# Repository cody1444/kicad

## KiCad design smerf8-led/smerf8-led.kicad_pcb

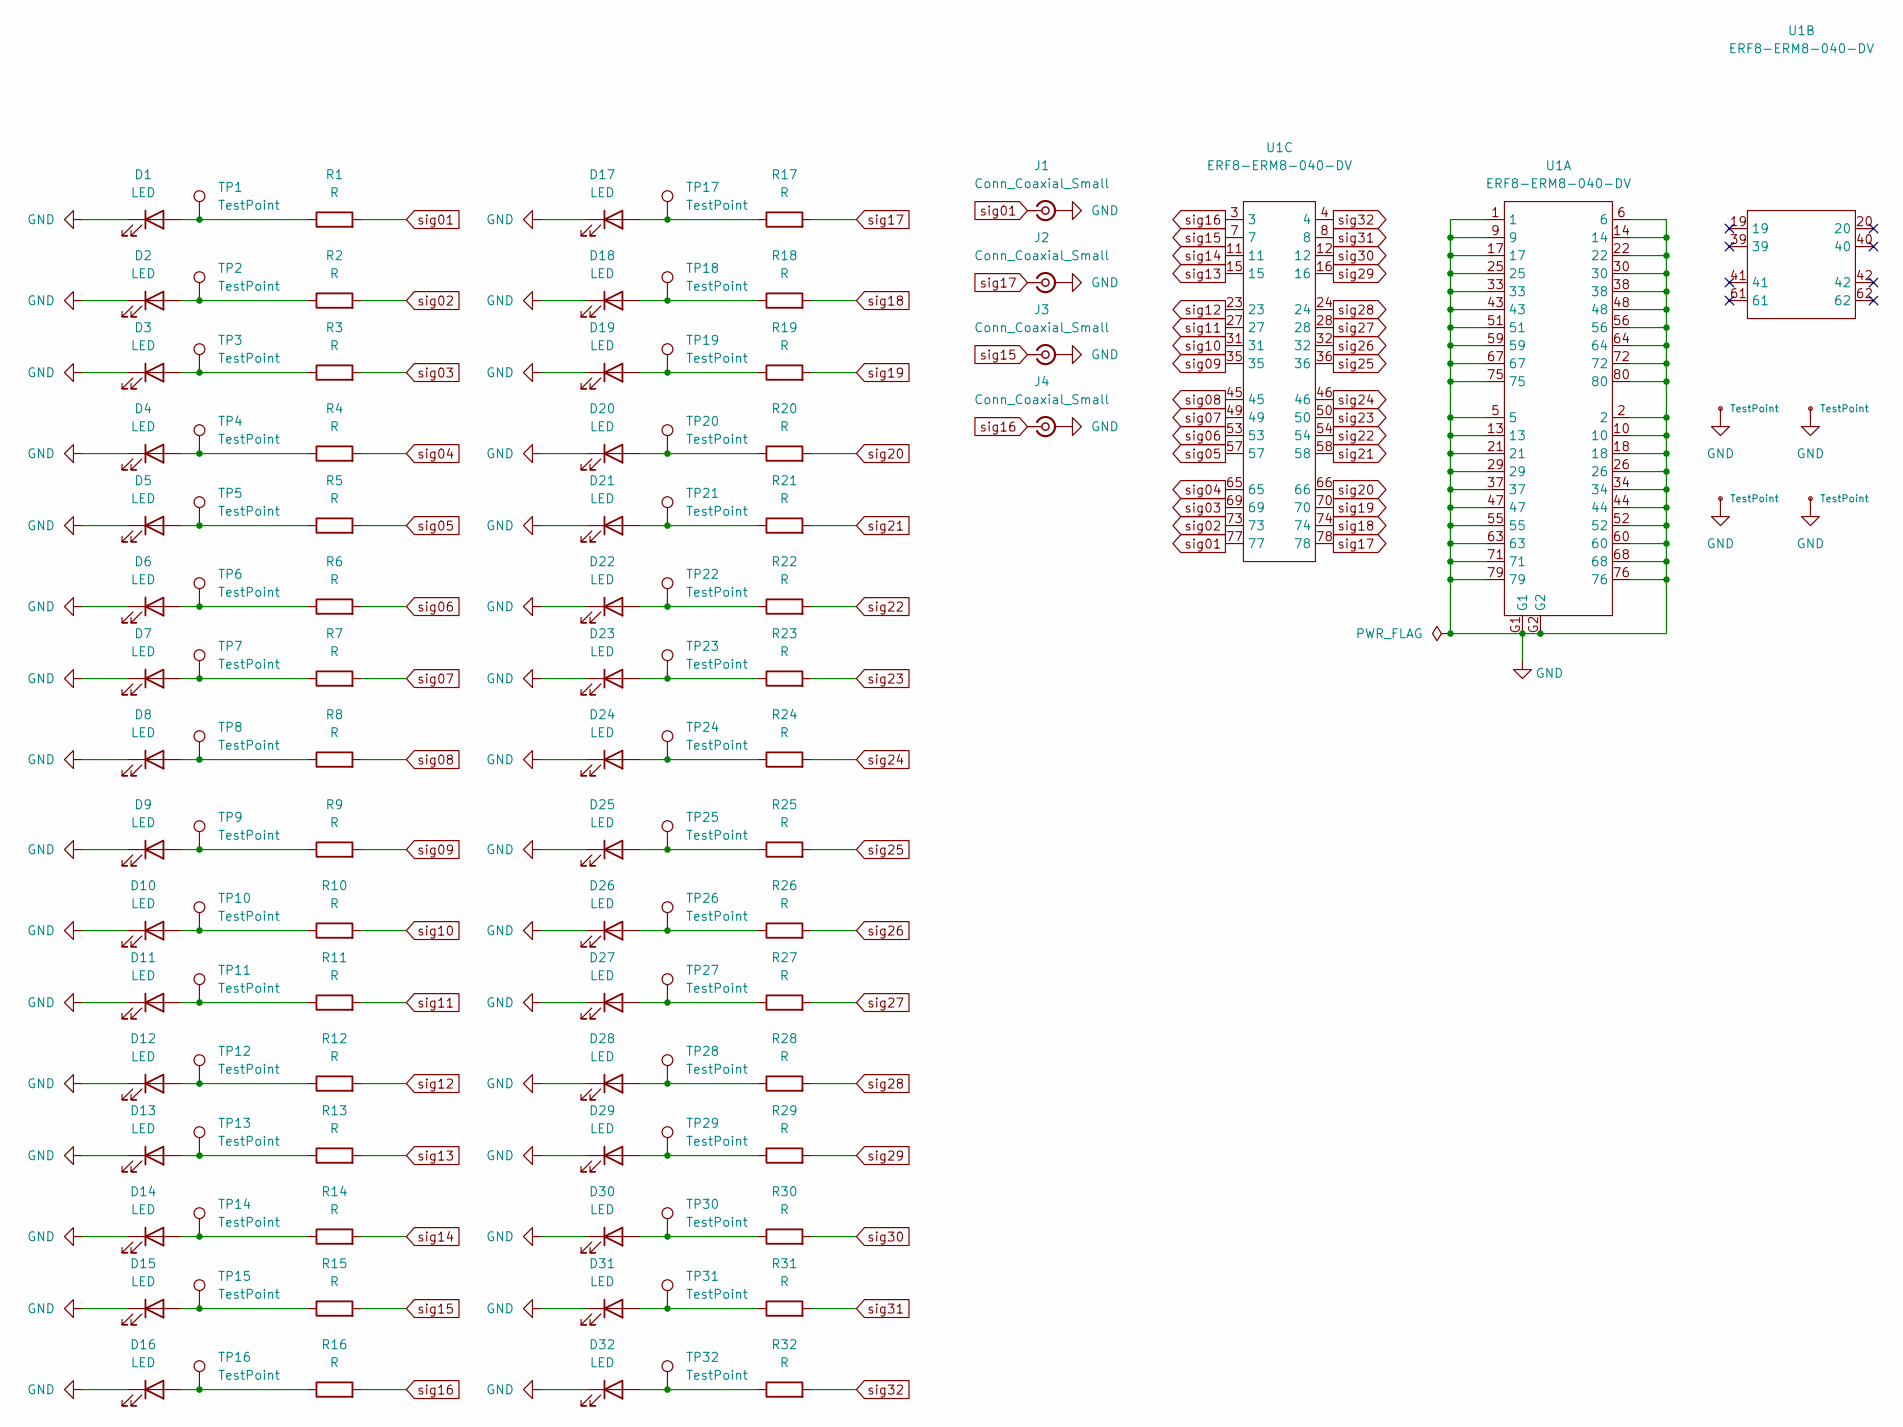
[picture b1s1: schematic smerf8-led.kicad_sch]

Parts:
D1, D2, D3, D4, D5, D6, D7, D8, D9, D10, D11, D12, D13, D14, D15, D16, D17, D18, D19, D20, D21, D22, D23, D24, D25, D26, D27, D28, D29, D30, D31, D32: LED; LED_0402_1005Metric
GND1, GND2, GND3, GND4: TestPoint; TestPoint_Plated_Hole_D2.0mm
J1, J2, J3, J4: Conn_Coaxial_Small; MMCX_Molex_73415-1471_Vertical
R1, R2, R3, R4, R5, R6, R7, R8, R9, R10, R11, R12, R13, R14, R15, R16, R17, R18, R19, R20, R21, R22, R23, R24, R25, R26, R27, R28, R29, R30, R31, R32: R; R_0603_1608Metric
TP1, TP2, TP3, TP4, TP5, TP6, TP7, TP8, TP9, TP10, TP11, TP12, TP13, TP14, TP15, TP16, TP17, TP18, TP19, TP20, TP21, TP22, TP23, TP24, TP25, TP26, TP27, TP28, TP29, TP30, TP31, TP32: TestPoint; TestPoint_Plated_Hole_D1.1mm
U1: ERF8-ERM8-040-DV; ERF8-040-EM2

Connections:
GND: D1.1 (K), D2.1 (K), D3.1 (K), D4.1 (K), D5.1 (K), D6.1 (K), D7.1 (K), D8.1 (K), D9.1 (K), D10.1 (K), D11.1 (K), D12.1 (K), D13.1 (K), D14.1 (K), D15.1 (K), D16.1 (K), D17.1 (K), D18.1 (K), D19.1 (K), D20.1 (K), D21.1 (K), D22.1 (K), D23.1 (K), D24.1 (K), D25.1 (K), D26.1 (K), D27.1 (K), D28.1 (K), D29.1 (K), D30.1 (K), D31.1 (K), D32.1 (K), GND1.1, GND2.1, GND3.1, GND4.1, J1.2 (Ext), J2.2 (Ext), J3.2 (Ext), J4.2 (Ext), U1.1, U1.2, U1.5, U1.6, U1.9, U1.10, U1.13, U1.14, U1.17, U1.18, U1.21, U1.22, U1.25, U1.26, U1.29, U1.30, U1.33, U1.34, U1.37, U1.38, U1.43, U1.44, U1.47, U1.48, U1.51, U1.52, U1.55, U1.56, U1.59, U1.60, U1.63, U1.64, U1.67, U1.68, U1.71, U1.72, U1.75, U1.76, U1.79, U1.80, U1.G1, U1.G2
unnamed: D1.2 (A), R1.1, TP1.1
unnamed: D2.2 (A), R2.1, TP2.1
unnamed: D3.2 (A), R3.1, TP3.1
unnamed: D4.2 (A), R4.1, TP4.1
unnamed: D5.2 (A), R5.1, TP5.1
unnamed: D6.2 (A), R6.1, TP6.1
unnamed: D7.2 (A), R7.1, TP7.1
unnamed: D8.2 (A), R8.1, TP8.1
unnamed: D9.2 (A), R9.1, TP9.1
unnamed: D10.2 (A), R10.1, TP10.1
unnamed: D11.2 (A), R11.1, TP11.1
unnamed: D12.2 (A), R12.1, TP12.1
unnamed: D13.2 (A), R13.1, TP13.1
unnamed: D14.2 (A), R14.1, TP14.1
unnamed: D15.2 (A), R15.1, TP15.1
unnamed: D16.2 (A), R16.1, TP16.1
unnamed: D17.2 (A), R17.1, TP17.1
unnamed: D18.2 (A), R18.1, TP18.1
unnamed: D19.2 (A), R19.1, TP19.1
unnamed: D20.2 (A), R20.1, TP20.1
unnamed: D21.2 (A), R21.1, TP21.1
unnamed: D22.2 (A), R22.1, TP22.1
unnamed: D23.2 (A), R23.1, TP23.1
unnamed: D24.2 (A), R24.1, TP24.1
unnamed: D25.2 (A), R25.1, TP25.1
unnamed: D26.2 (A), R26.1, TP26.1
unnamed: D27.2 (A), R27.1, TP27.1
unnamed: D28.2 (A), R28.1, TP28.1
unnamed: D29.2 (A), R29.1, TP29.1
unnamed: D30.2 (A), R30.1, TP30.1
unnamed: D31.2 (A), R31.1, TP31.1
unnamed: D32.2 (A), R32.1, TP32.1
sig01: J1.1 (In), R1.2, U1.77
sig02: R2.2, U1.73
sig03: R3.2, U1.69
sig04: R4.2, U1.65
sig05: R5.2, U1.57
sig06: R6.2, U1.53
sig07: R7.2, U1.49
sig08: R8.2, U1.45
sig09: R9.2, U1.35
sig10: R10.2, U1.31
sig11: R11.2, U1.27
sig12: R12.2, U1.23
sig13: R13.2, U1.15
sig14: R14.2, U1.11
sig15: J3.1 (In), R15.2, U1.7
sig16: J4.1 (In), R16.2, U1.3
sig17: J2.1 (In), R17.2, U1.78
sig18: R18.2, U1.74
sig19: R19.2, U1.70
sig20: R20.2, U1.66
sig21: R21.2, U1.58
sig22: R22.2, U1.54
sig23: R23.2, U1.50
sig24: R24.2, U1.46
sig25: R25.2, U1.36
sig26: R26.2, U1.32
sig27: R27.2, U1.28
sig28: R28.2, U1.24
sig29: R29.2, U1.16
sig30: R30.2, U1.12
sig31: R31.2, U1.8
sig32: R32.2, U1.4

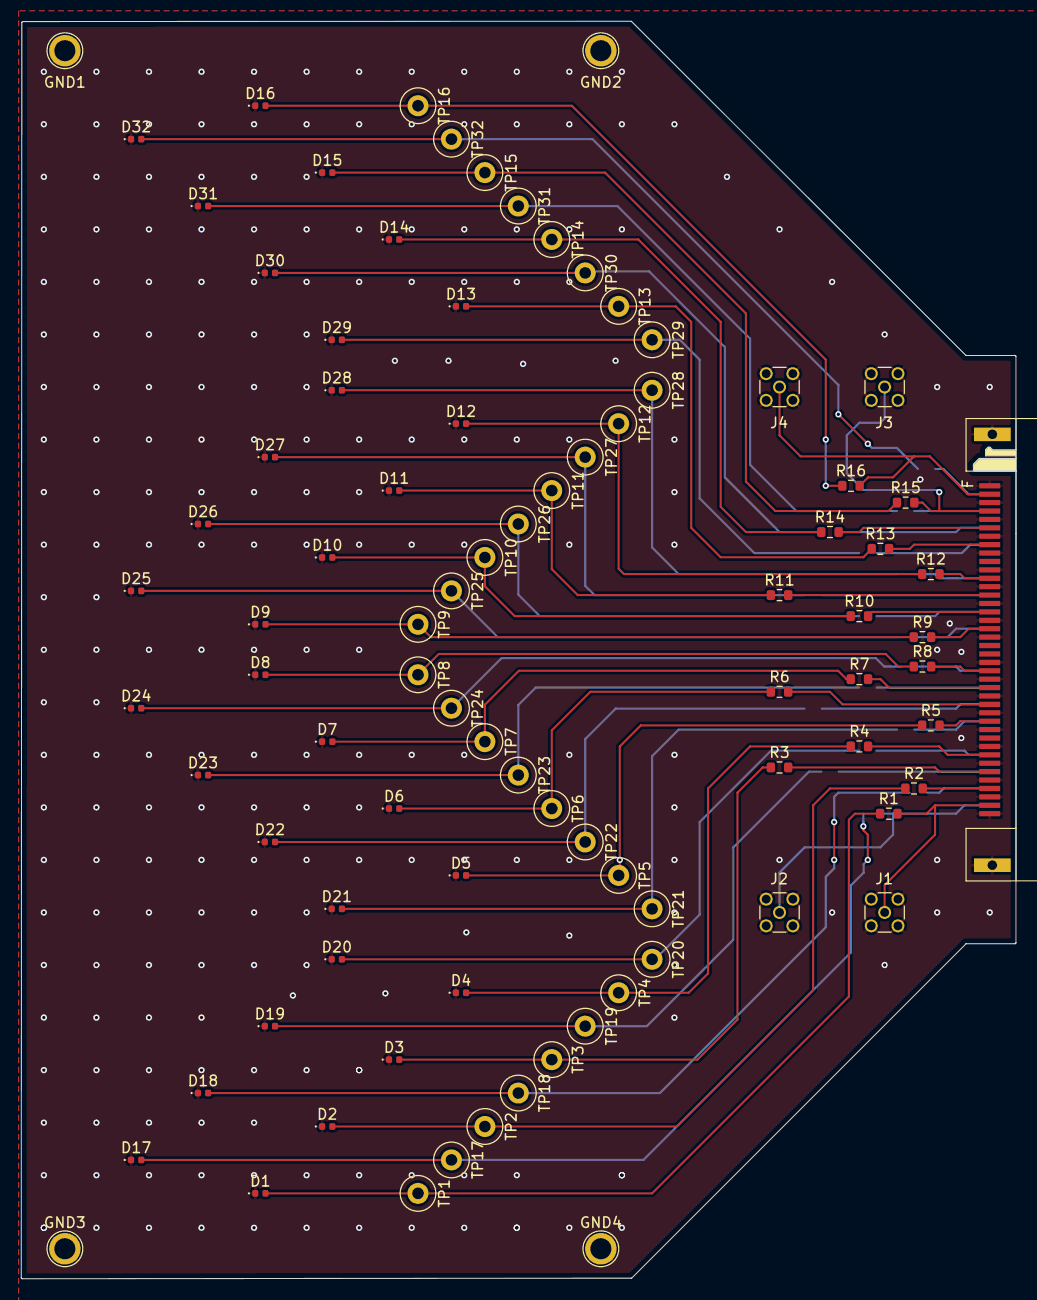
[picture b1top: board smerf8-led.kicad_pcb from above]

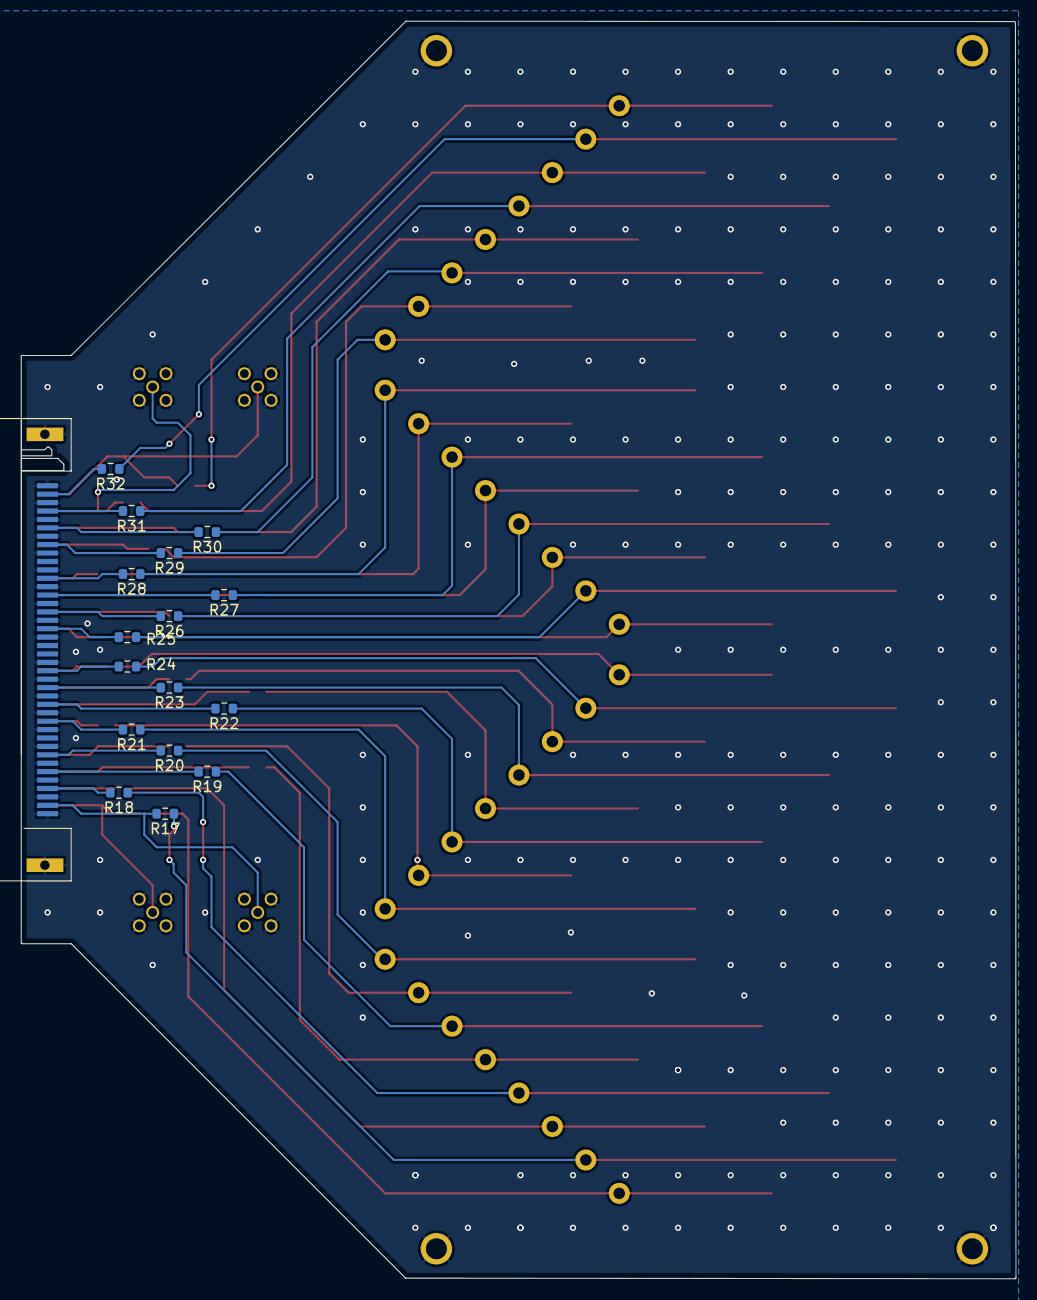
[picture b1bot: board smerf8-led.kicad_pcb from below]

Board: 2 copper layers, 94.7 x 119.6 mm, 105 parts (16 on the bottom side), 65 nets.

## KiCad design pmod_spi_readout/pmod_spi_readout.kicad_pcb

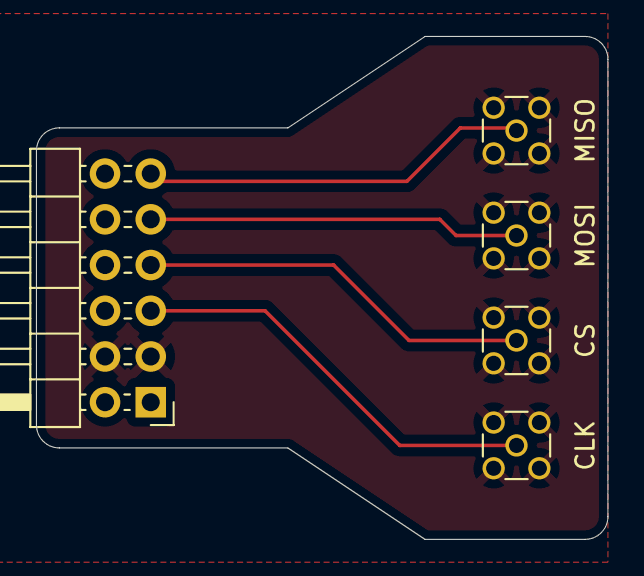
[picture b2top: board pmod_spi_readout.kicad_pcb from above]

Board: 2 copper layers, 31.8 x 27.9 mm, 5 parts (0 on the bottom side), 5 nets.

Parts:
CLK: Conn_Coaxial_Small; MMCX_Molex_73415-1471_Vertical
CS: Conn_Coaxial_Small; MMCX_Molex_73415-1471_Vertical
J1: pmod2x6socket; PinHeader_2x06_P2.54mm_Horizontal
MISO: Conn_Coaxial_Small; MMCX_Molex_73415-1471_Vertical
MOSI: Conn_Coaxial_Small; MMCX_Molex_73415-1471_Vertical

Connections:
GND: CLK.2 (Ext), CS.2 (Ext), J1.3, J1.4, MISO.2 (Ext), MOSI.2 (Ext)
unnamed: CLK.1 (In), J1.5
unnamed: CS.1 (In), J1.7
unnamed: J1.9, MOSI.1 (In)
unnamed: J1.11, MISO.1 (In)

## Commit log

2025-07-16 added smerf-led
2025-07-17 board 90% done
2025-07-17 first draft done!
2025-07-18 pmod mcx connector bank
